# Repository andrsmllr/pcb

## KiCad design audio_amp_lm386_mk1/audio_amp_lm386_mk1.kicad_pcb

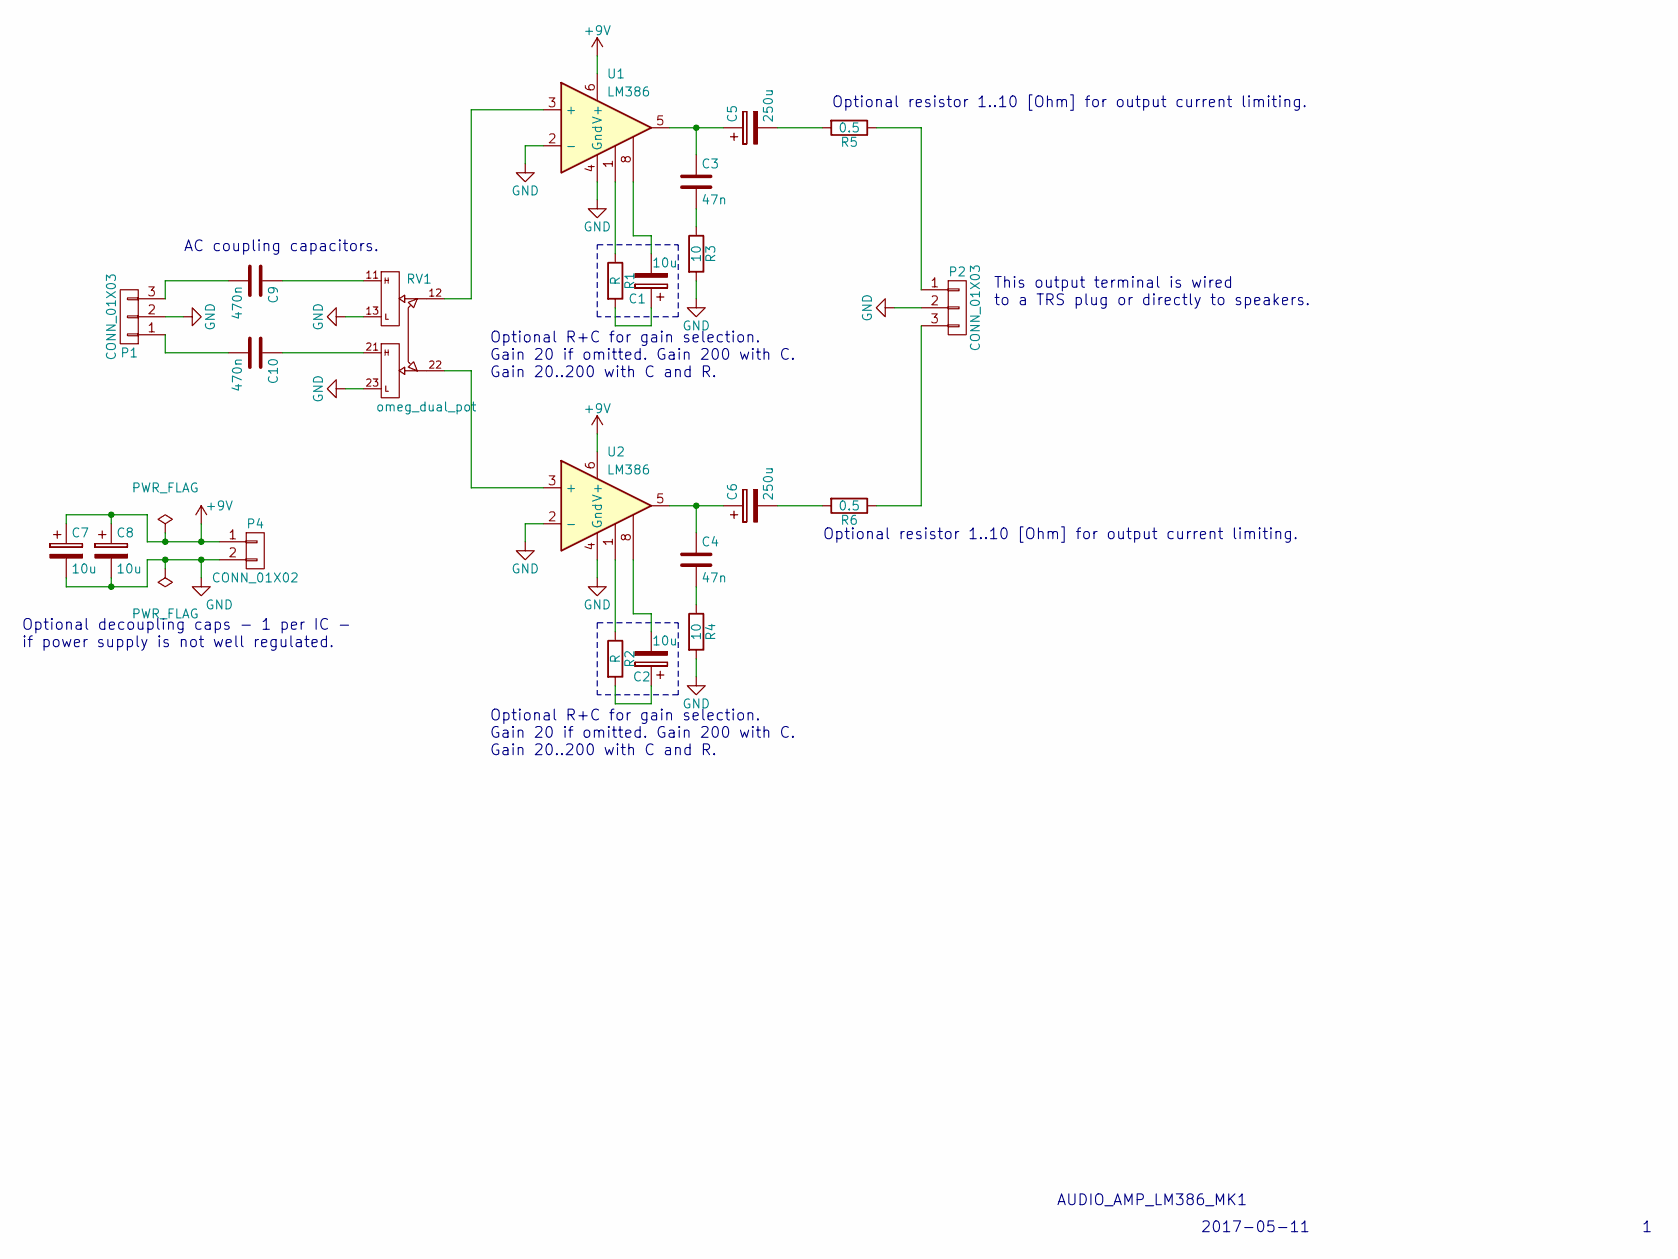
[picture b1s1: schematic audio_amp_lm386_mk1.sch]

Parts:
C1, C2: 10u; C_Radial_D6.3_L11.2_P2.5
C3, C4: 47n; C_Disc_D3_P2.5
C5, C6: 250u; C_Radial_D6.3_L11.2_P2.5
C7, C8: 10u; C_Radial_D10_L25_P5
C9, C10: 470n; C_Disc_D3_P2.5
P1, P2: CONN_01X03; WAGO_734_3pin_Straight_RuggedPads
P4: CONN_01X02; WAGO_734_2pin_Straight_RuggedPads
R1, R2: R; Resistor_Horizontal_RM15mm
R3, R4: 10; Resistor_Horizontal_RM15mm
R5, R6: 0.5; Resistor_Horizontal_RM15mm
RV1: omeg_dual_pot; Potentiometer_Alps-RK163-double_20mm
U1, U2: LM386; DIP-8_W7.62mm_LongPads

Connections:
+9V: C7.1, C8.1, P4.1, U1.6 (V+), U2.6 (V+)
GND: C7.2, C8.2, P1.2, P2.2, P4.2, R3.2, R4.2, RV1.13 (3), RV1.23 (6), U1.2 (-), U1.4 (Gnd), U2.2 (-), U2.4 (Gnd)
unnamed: C1.1, R1.2
unnamed: C1.2, U1.8
unnamed: C2.1, R2.2
unnamed: C2.2, U2.8
unnamed: C3.1, C5.1, U1.5
unnamed: C3.2, R3.1
unnamed: C4.1, C6.1, U2.5
unnamed: C4.2, R4.1
unnamed: C5.2, R5.2
unnamed: C6.2, R6.2
unnamed: C9.1, RV1.11 (1)
unnamed: C9.2, P1.3
unnamed: C10.1, RV1.21 (4)
unnamed: C10.2, P1.1
unnamed: P2.1, R5.1
unnamed: P2.3, R6.1
unnamed: R1.1, U1.1
unnamed: R2.1, U2.1
unnamed: RV1.12 (2), U1.3 (+)
unnamed: RV1.22 (5), U2.3 (+)

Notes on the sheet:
Optional R+C for gain selection. Gain 20 if omitted. Gain 200 with C. Gain 20..200 with C and R.
Optional decoupling caps - 1 per IC - if power supply is not well regulated.
Optional resistor 1..10 [Ohm] for output current limiting.
AC coupling capacitors.
This output terminal is wired to a TRS plug or directly to speakers.
AUDIO_AMP_LM386_MK1
2017-05-11

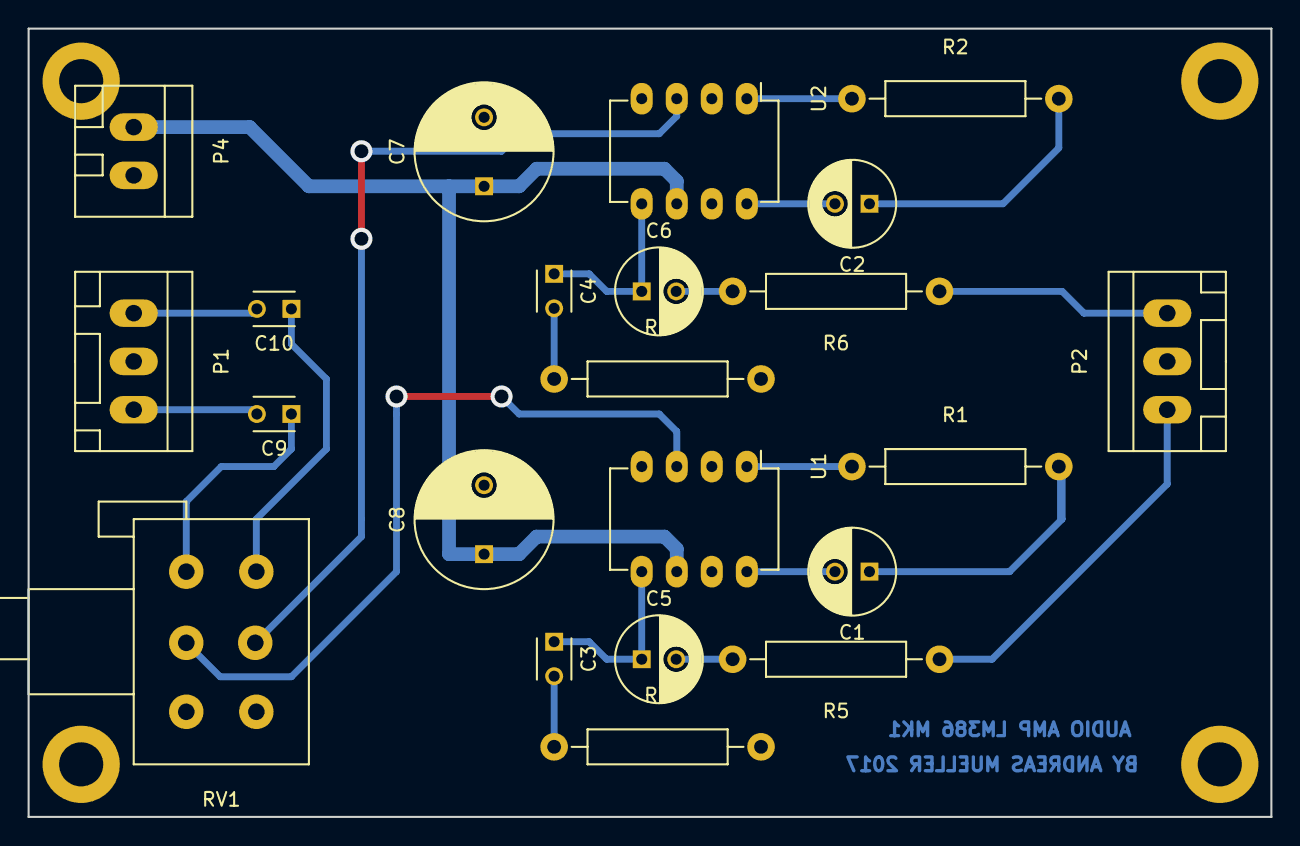
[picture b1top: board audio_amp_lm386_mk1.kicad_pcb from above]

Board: 2 copper layers, 90.1 x 57.2 mm, 22 parts (0 on the bottom side), 22 nets.

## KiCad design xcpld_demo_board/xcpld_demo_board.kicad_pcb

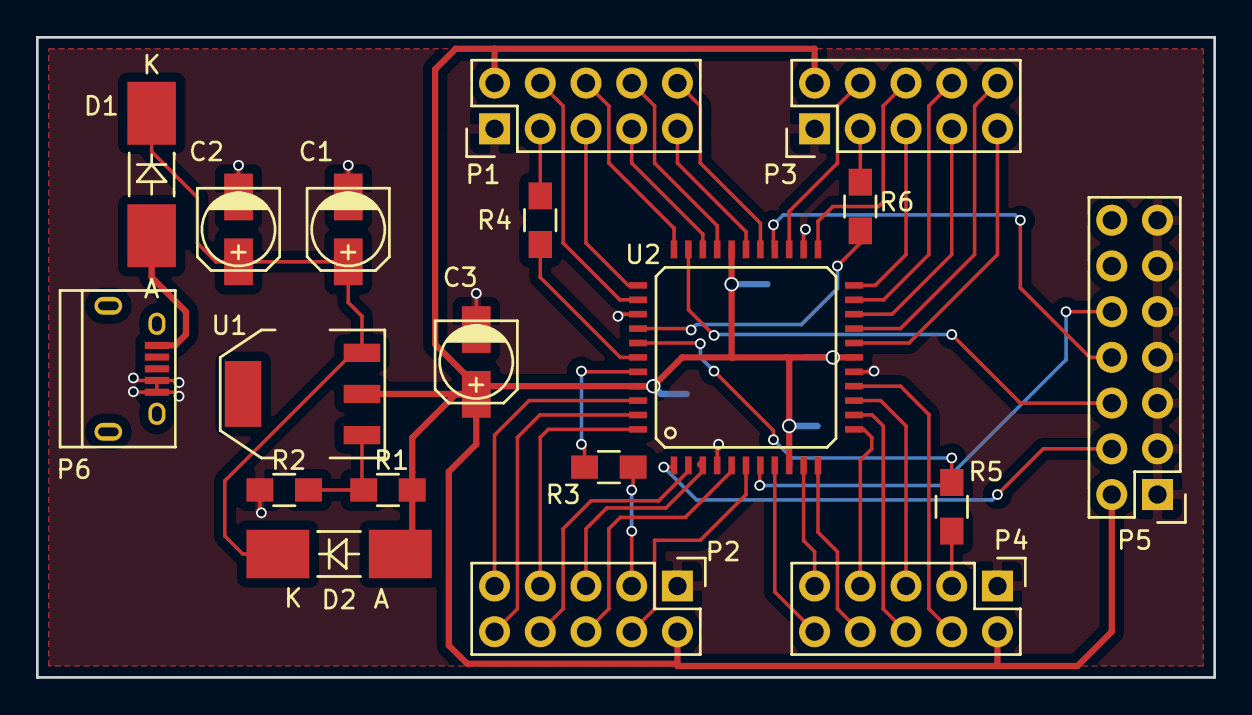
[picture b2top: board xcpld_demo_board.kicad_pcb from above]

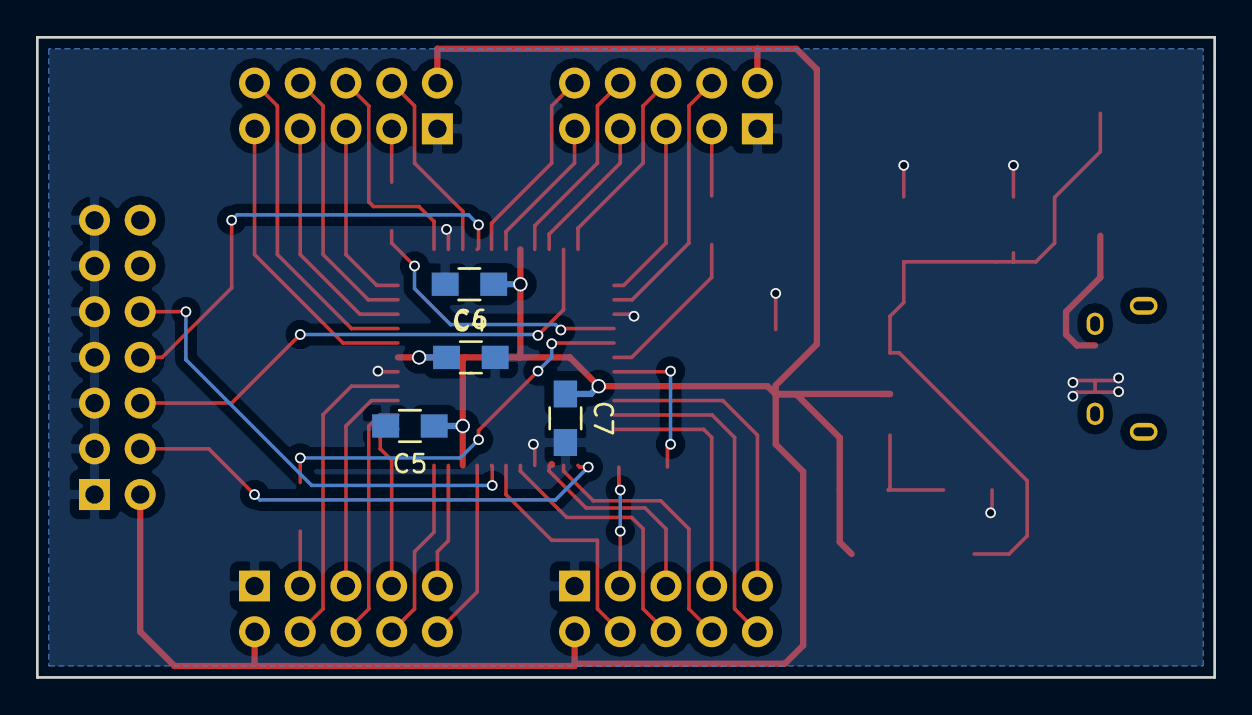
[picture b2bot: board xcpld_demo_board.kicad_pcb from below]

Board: 2 copper layers, 65.4 x 35.6 mm, 23 parts (4 on the bottom side), 45 nets.

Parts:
C1, C2, C3: CP1; c_elec_4x5.3
C4, C5, C6, C7: C; R_0805_HandSoldering
D1, D2: D_Schottky; MELF_Handsoldering
P1, P2, P3, P4: CONN_02X05; Pin_Header_Straight_2x05
P5: CONN_02X07; Pin_Header_Straight_2x07
P6: USB_B; USB_Micro-B
R1, R2: R; R_0805_HandSoldering
R3, R4, R5, R6: 22; R_0805_HandSoldering
U1: LM317EMP; SOT-223
U2: XCR3064-VQ44; myFootprint

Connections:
+3V3: C3.1, C4.1, C5.1, C6.1, C7.1, D2.2, P1.2, P2.2, P3.2, P4.2, P5.2, R1.1, U1.2, U2.9, U2.17, U2.29, U2.41
+5V: D1.2, P6.1
COOL_A0: P1.4, U2.35
COOL_A1: P1.5, U2.34
COOL_A7: P1.6, U2.33
COOL_A9: P1.7, U2.31
COOL_A10: P1.8, U2.30
COOL_A13: P1.9, U2.28
COOL_A14: P1.10, U2.27
COOL_B0: P2.9, U2.42
COOL_B1: P2.10, U2.43
COOL_B2: P2.7, U2.44
COOL_B9: P2.8, U2.2
COOL_B10: P2.5, U2.3
COOL_B13: P2.6, U2.5
COOL_B14: P2.4, U2.6
COOL_C1: P3.4, U2.25
COOL_C3: P3.6, U2.23
COOL_C8: P3.5, U2.22
COOL_C9: P3.8, U2.21
COOL_C10: P3.7, U2.20
COOL_C11: P3.10, U2.19
COOL_C12: P3.9, U2.18
COOL_CLK0: P2.3, R3.2
COOL_CLK1: P1.3, R4.2
COOL_CLK2: P4.3, R5.2
COOL_CLK3: P3.3, R6.2
COOL_D1: P4.10, U2.8
COOL_D3: P4.9, U2.10
COOL_D4: P4.8, U2.11
COOL_D8: P4.7, U2.12
COOL_D9: P4.6, U2.13
COOL_D10: P4.5, U2.14
COOL_D11: P4.4, U2.15
COOL_JTAG_TCK: P5.8, U2.26
COOL_JTAG_TDI: P5.4, U2.1
COOL_JTAG_TDO: P5.6, U2.32
COOL_JTAG_TMS: P5.10, U2.7
COOL_PORT_EN: C1.2, C2.2, C3.2, C4.2, C5.2, C6.2, C7.2, P1.1, P2.1, P3.1, P4.1, P5.1, P5.3, P5.5, P5.7, P5.9, P5.11, P5.13, P6.4, P6.5, R2.2, U2.4, U2.16, U2.24, U2.36
unnamed: C1.1, C2.1, D1.1, D2.1, U1.3
unnamed: R1.2, R2.1, U1.1
unnamed: R3.1, U2.40
unnamed: R4.1, U2.39
unnamed: R5.1, U2.38
unnamed: R6.1, U2.37

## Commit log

2016-07-30 New project for Xilinx Platform Cable III
2016-08-13 New project for Xilinx CPLD demo board (KiCad)
2016-10-09 Update schematic and layout
2017-05-11 Update schematics and layouts (pin progress)
2017-11-15 Commit current progress (unknown changes).
2017-11-17 Initial commit for 7400_lowend_pwm (draft).
2017-11-17 Initial commmit of fan_rot_sense_disp (draft).
2017-12-14 Update progress
2018-03-27 Update layout, increase via size and improve routing around vias.
